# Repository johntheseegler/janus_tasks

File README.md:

# *****PS******
I am GOOD at coding but I chose to do pcb first and spent too much time, and that's the only reason I used chat gpt.

***TASK_1****

task_1_atm1 is the ardiomo code for implementing moving average.

This code uses simple moving average, it simply takes a set amount of data (say 5) and returns the average 
it helps to smooth out data.

Exponential moving average gives more weight to current data

1 MIN LEFT CAN I EXPLAIN IN INTERVIEW PLS

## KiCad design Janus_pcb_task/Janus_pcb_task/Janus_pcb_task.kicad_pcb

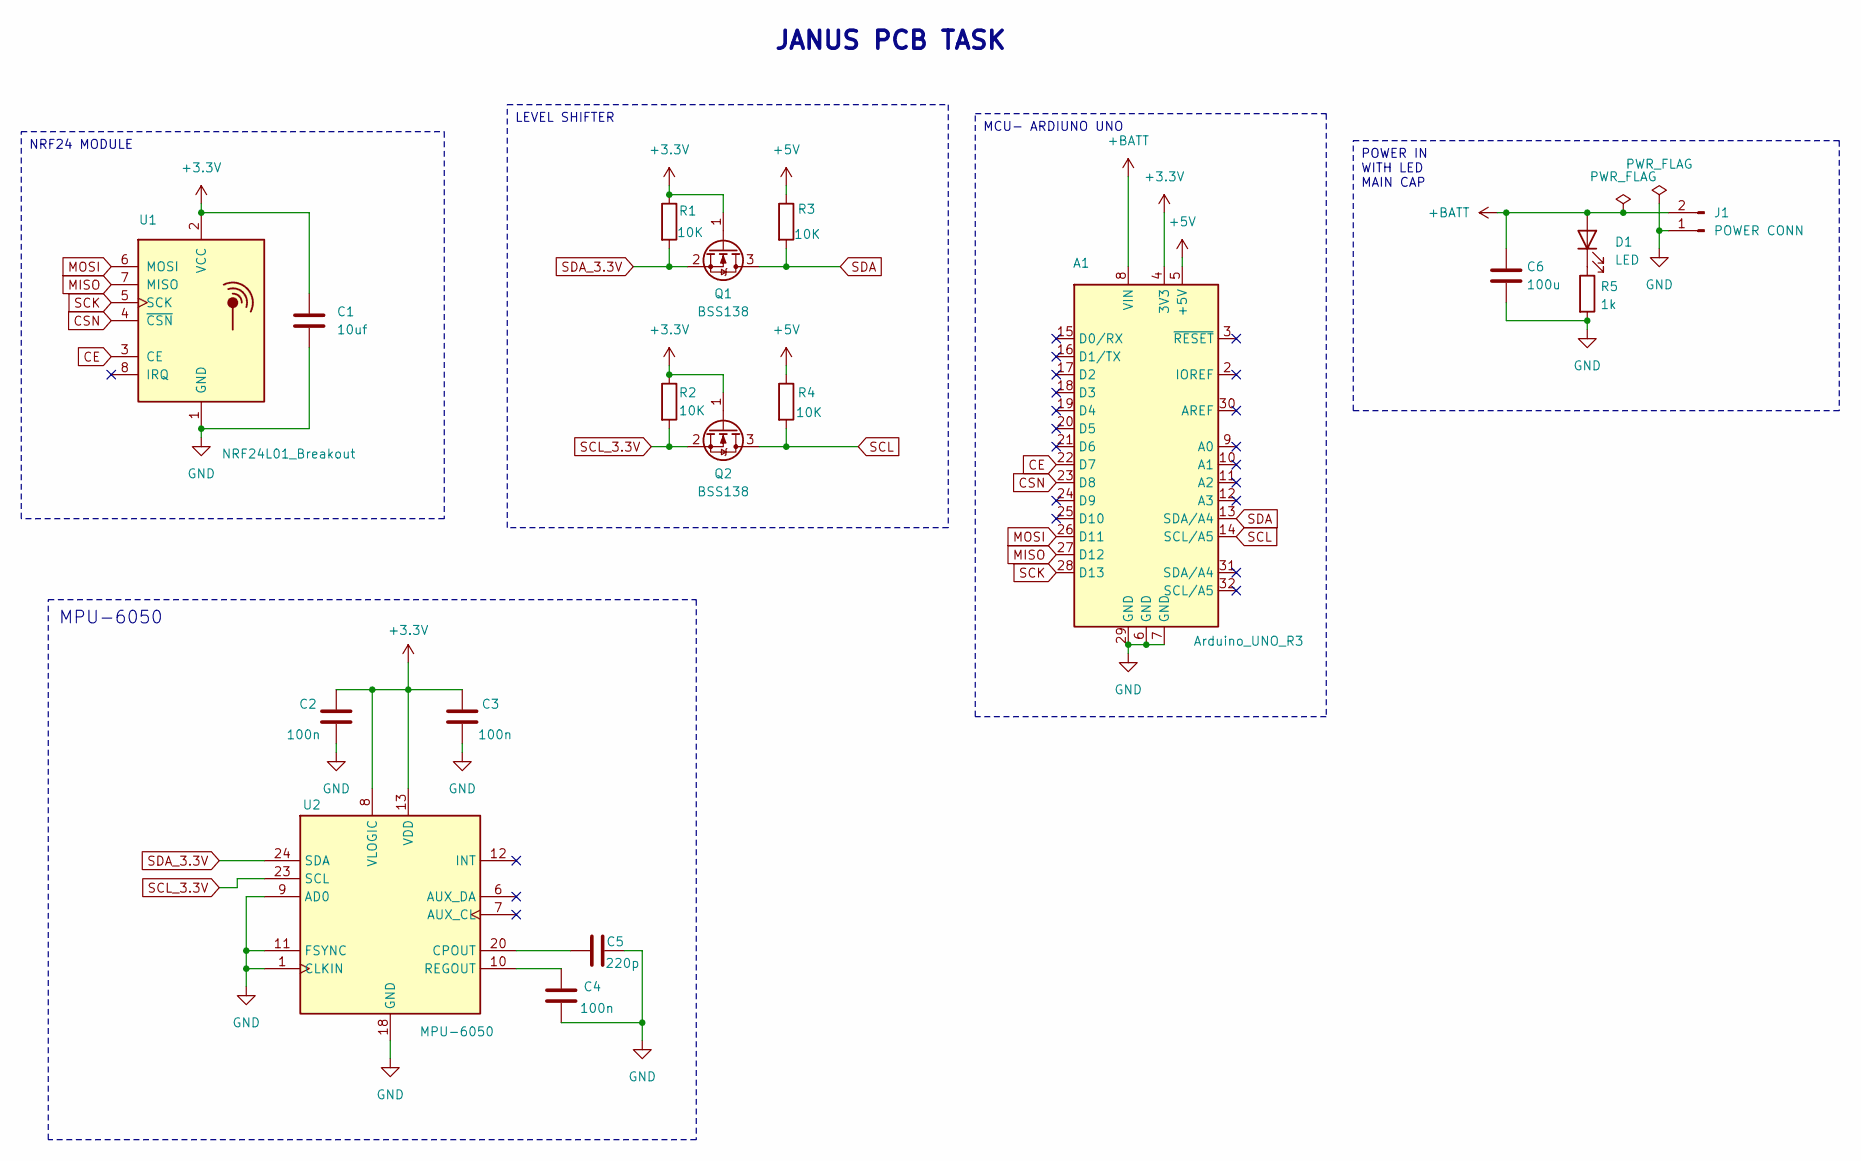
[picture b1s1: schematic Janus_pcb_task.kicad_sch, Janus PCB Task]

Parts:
A1: Arduino_UNO_R3
C1: 10uf; C_Radial_D4.0mm_H5.0mm_P1.50mm
C2, C3, C4: 100n; C_0603_1608Metric
C5: 220p; C_0603_1608Metric
C6: 100u; C_Radial_D5.0mm_H7.0mm_P2.00mm
D1: LED; LED_0603_1608Metric
J1: POWER CONN; JST_XH_B2B-XH-A_1x02_P2.50mm_Vertical
Q1, Q2: BSS138; SOT-23
R1, R2, R3, R4: 10K; R_0603_1608Metric
R5: 1k; R_0603_1608Metric
U1: NRF24L01_Breakout; nRF24L01_Breakout
U2: MPU-6050; InvenSense_QFN-24_4x4mm_P0.5mm

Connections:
+3.3V: A1.4 (3V3), C1.1, C2.2, C3.2, Q1.1 (G), Q2.1 (G), R1.1, R2.1, U1.2 (VCC), U2.8 (VLOGIC), U2.13 (VDD)
+5V: A1.5 (+5V), R3.1, R4.1
+BATT: A1.8 (VIN), C6.1, D1.2 (A), J1.2
CE: A1.22 (D7), U1.3 (CE)
CSN: A1.23 (D8), U1.4 (~CSN)
GND: A1.6 (GND), A1.7 (GND), A1.29 (GND), C1.2, C2.1, C3.1, C4.2, C5.1, C6.2, J1.1, R5.2, U1.1 (GND), U2.1 (CLKIN), U2.9 (AD0), U2.11 (FSYNC), U2.18 (GND)
MISO: A1.27 (D12), U1.7 (MISO)
MOSI: A1.26 (D11), U1.6 (MOSI)
unnamed: D1.1 (K), R5.1
unnamed: C5.2, U2.20 (CPOUT)
unnamed: C4.1, U2.10 (REGOUT)
SCK: A1.28 (D13), U1.5 (SCK)
SCL: A1.14 (SCL/A5), Q2.3 (D), R4.2
SCL_3.3V: Q2.2 (S), R2.2, U2.23 (SCL)
SDA: A1.13 (SDA/A4), Q1.3 (D), R3.2
SDA_3.3V: Q1.2 (S), R1.2, U2.24 (SDA)

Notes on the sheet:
LEVEL SHIFTER
NRF24 MODULE
POWER IN WITH LED MAIN CAP
MCU- ARDIUNO UNO
MPU-6050
JANUS PCB TASK

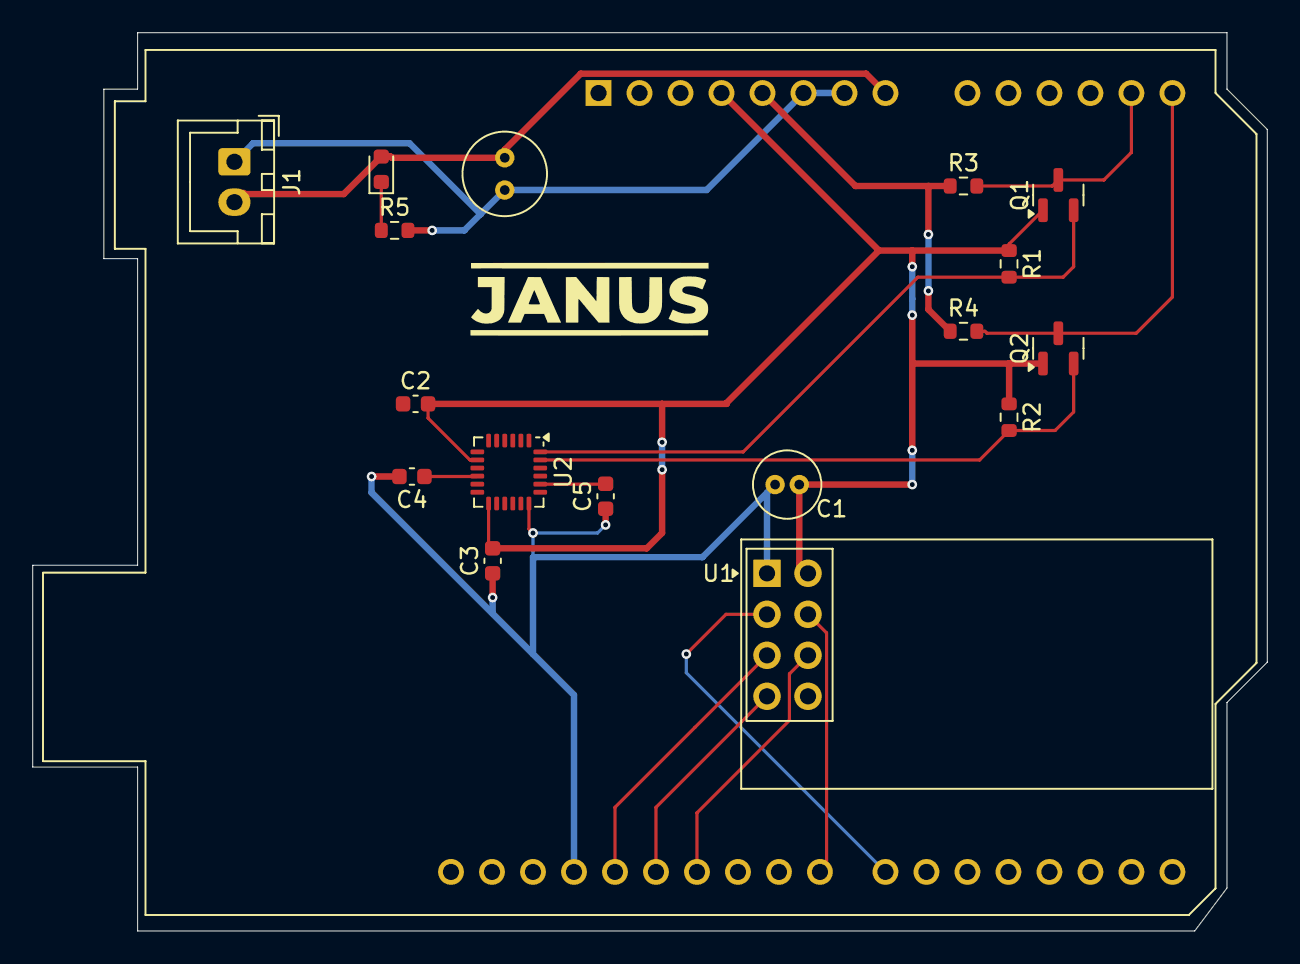
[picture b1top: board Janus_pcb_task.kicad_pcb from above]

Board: 2 copper layers, 76.5 x 55.7 mm, 18 parts (0 on the bottom side), 16 nets.
